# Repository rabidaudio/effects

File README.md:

# Custom effects pedals

Homemade guitar/bass effects pedals.

- [Splitter](/splitter)
- [Bass Chorus (WIP)](/chorus)

## License

Schematics, board layouts, documentation, etc. is licensed under [Creative Commons Attribution-NonCommercial-ShareAlike 4.0 International License](http://creativecommons.org/licenses/by-nc-sa/4.0/).

If you're interested in commercial use, please ask first.

Any source code is licensed under [MIT](SOFTWARE_LICENSE).

## Notes

```
jacks: neutrik from shared effects lib
capacitors: Capacitor_THT:C_Rect_L7.0mm_W2.5mm_P5.00mm
resistors (flush): Resistor_THT:R_Axial_DIN0207_L6.3mm_D2.5mm_P10.16mm_Horizontal
alpha 9mm pots: Potentiometer_THT:Potentiometer_Alpha_RD901F-40-00D_Single_Vertical

CASE:
outer dims: 120x65 mm
wall depth: 2 mm
usable inner space: 102x60 mm
screw area: 8.6x8.6 mm

center point: 160.02 x 101.6 mm

pots minimum 12mm from top
stomp switch ~34mm from bottom
```

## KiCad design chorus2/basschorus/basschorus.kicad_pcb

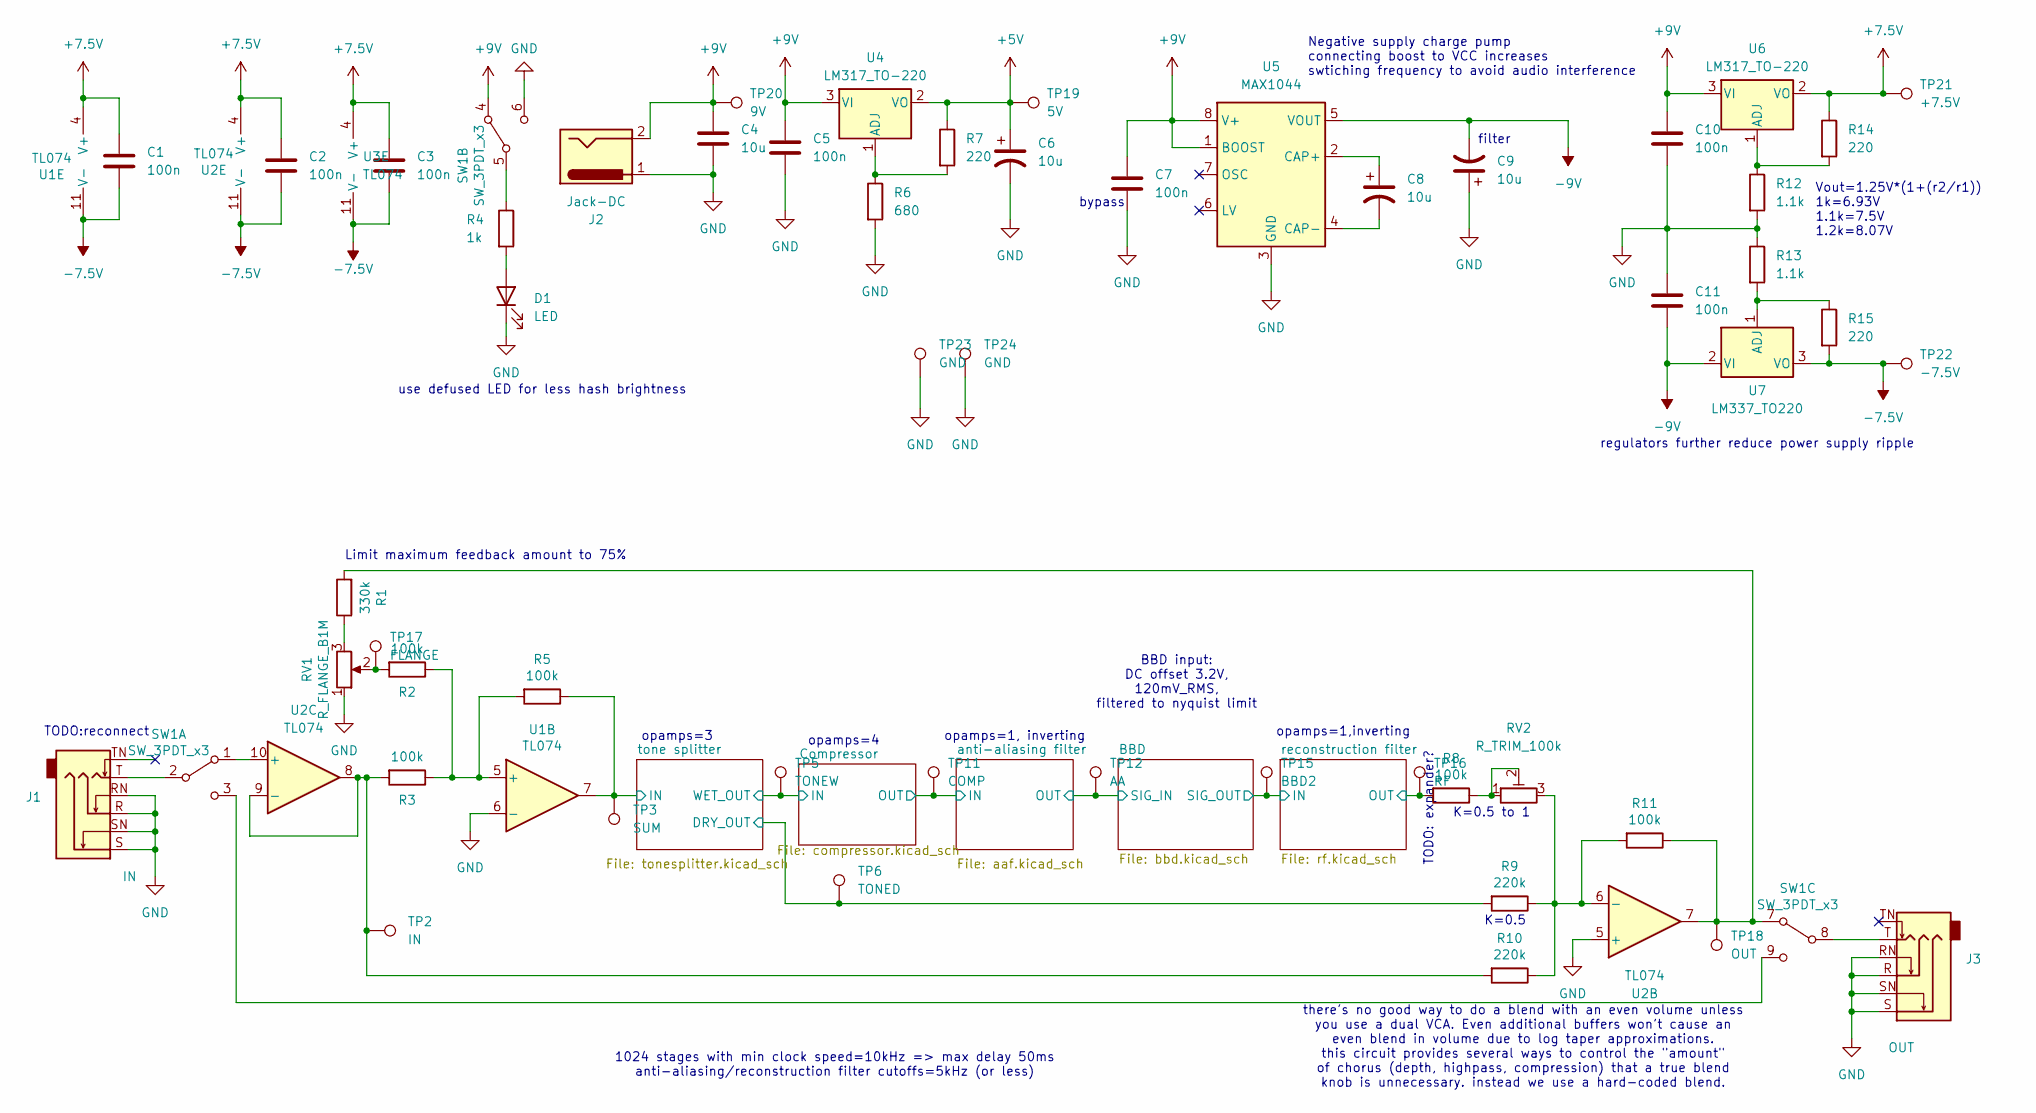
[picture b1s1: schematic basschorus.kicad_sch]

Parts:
C1, C2, C3, C5, C7, C10, C11: 100n; C_Rect_L7.0mm_W2.5mm_P5.00mm
C4, C6, C8, C9: 10u; CP_Radial_D8.0mm_P5.00mm
D1: LED; LED_Rectangular_W5.0mm_H2.0mm
J1: IN; JackHeaders
J2: Jack-DC; PinSocket_1x02_P2.54mm_Vertical
J3: OUT; JackHeaders
R1: 330k; R_Axial_DIN0204_L3.6mm_D1.6mm_P2.54mm_Vertical
R2, R3, R5, R8, R11: 100k; R_Axial_DIN0204_L3.6mm_D1.6mm_P2.54mm_Vertical
R4: 1k; R_Axial_DIN0204_L3.6mm_D1.6mm_P2.54mm_Vertical
R6: 680; R_Axial_DIN0204_L3.6mm_D1.6mm_P2.54mm_Vertical
R7, R14, R15: 220; R_Axial_DIN0204_L3.6mm_D1.6mm_P2.54mm_Vertical
R9, R10: 220k; R_Axial_DIN0204_L3.6mm_D1.6mm_P2.54mm_Vertical
R12, R13: 1.1k; R_Axial_DIN0204_L3.6mm_D1.6mm_P2.54mm_Vertical
RV1: R_FLANGE_B1M; Potentiometer_Alpha_RD901F-40-00D_Single_Vertical_CircularH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
RV2: R_TRIM_100k; Potentiometer_Vishay_T73YP_Vertical
SW1: SW_3PDT_x3; PinHeader_1x09_P2.54mm_Vertical
TP2: IN; TestPoint_THTPad_2.5x2.5mm_Drill1.2mm
TP3: SUM; TestPoint_THTPad_2.5x2.5mm_Drill1.2mm
TP5: TONEW; TestPoint_THTPad_2.5x2.5mm_Drill1.2mm
TP6: TONED; TestPoint_THTPad_2.5x2.5mm_Drill1.2mm
TP11: COMP; TestPoint_THTPad_2.5x2.5mm_Drill1.2mm
TP12: AA; TestPoint_THTPad_2.5x2.5mm_Drill1.2mm
TP15: BBD2; TestPoint_THTPad_2.5x2.5mm_Drill1.2mm
TP16: RF; TestPoint_THTPad_2.5x2.5mm_Drill1.2mm
TP17: FLANGE; TestPoint_THTPad_2.5x2.5mm_Drill1.2mm
TP18: OUT; TestPoint_THTPad_2.5x2.5mm_Drill1.2mm
TP19: 5V; TestPoint_THTPad_2.5x2.5mm_Drill1.2mm
TP20: 9V; TestPoint_THTPad_2.5x2.5mm_Drill1.2mm
TP21: +7.5V; TestPoint_THTPad_2.5x2.5mm_Drill1.2mm
TP22: -7.5V; TestPoint_THTPad_2.5x2.5mm_Drill1.2mm
TP23, TP24: GND; TestPoint_THTPad_2.5x2.5mm_Drill1.2mm
U1, U2, U3: TL074; SO-14_3.9x8.65mm_P1.27mm
U4, U6: LM317_TO-220; TO-220-3_Vertical
U5: MAX1044; DIP-8_W7.62mm
U7: LM337_TO220; TO-220-3_Vertical

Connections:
+5V: C6.1, R7.1, TP19.1, U4.2 (VO); also elsewhere on the board
+7.5V: C1.1, C2.1, C3.1, R14.1, TP21.1, U1.4 (V+), U2.4 (V+), U3.4 (V+), U6.2 (VO)
+9V: C4.1, C5.1, C7.1, C10.1, J2.2, SW1.4 (A), TP20.1, U4.3 (VI), U5.1 (BOOST), U5.8 (V+), U6.3 (VI)
-7.5V: C1.2, C2.2, C3.2, R15.2, TP22.1, U1.11 (V-), U2.11 (V-), U3.11 (V-), U7.3 (VO)
-9V: C9.2, C11.2, U5.5 (VOUT), U7.2 (VI)
/BBD/SIG_IN: TP12.1; also elsewhere on the board
/BBD/SIG_OUT: TP15.1; also elsewhere on the board
/Compressor/IN: TP5.1; also elsewhere on the board
/Compressor/OUT: TP11.1; also elsewhere on the board
/reconstruction filter/OUT: R8.2, TP16.1; also elsewhere on the board
/tone splitter/DRY_OUT: R9.2, TP6.1; also elsewhere on the board
/tone splitter/IN: R5.1, TP3.1, U1.7; also elsewhere on the board
GND: C4.2, C5.2, C6.2, C7.2, C9.1, C10.2, C11.1, D1.1 (K), J1.R, J1.RN, J1.S, J1.SN, J2.1, J3.R, J3.RN, J3.S, J3.SN, R6.2, R12.2, R13.1, RV1.1, SW1.6 (C), TP23.1, TP24.1, U1.6 (-), U2.5 (+), U5.3 (GND); also elsewhere on the board
unnamed: D1.2 (A), R4.2
unnamed: R1.1, RV1.3
unnamed: R2.2, RV1.2, TP17.1
unnamed: R8.1, RV2.1, RV2.2
unnamed: SW1.1 (A), U2.10 (+)
unnamed: J1.T, SW1.2 (B)
unnamed: SW1.3 (C), SW1.9 (C)
unnamed: R4.1, SW1.5 (B)
unnamed: R1.2, R11.1, SW1.7 (A), TP18.1, U2.7
unnamed: J3.T, SW1.8 (B)
unnamed: R2.1, R3.1, R5.2, U1.5 (+)
unnamed: R9.1, R10.1, R11.2, RV2.3, U2.6 (-)
unnamed: R3.2, R10.2, TP2.1, U2.8, U2.9 (-)
unnamed: R6.1, R7.2, U4.1 (ADJ)
unnamed: C8.1, U5.2 (CAP+)
unnamed: C8.2, U5.4 (CAP-)
unnamed: R12.1, R14.2, U6.1 (ADJ)
unnamed: R13.2, R15.1, U7.1 (ADJ)

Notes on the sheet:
TODO: expander?
Vout=1.25V*(1+(r2/r1)) 1k=6.93V 1.1k=7.5V 1.2k=8.07V
opamps=1,inverting
TODO:reconnect
opamps=1, inverting
Negative supply charge pump connecting boost to VCC increases swtiching frequency to avoid audio interference
K=0.5
regulators further reduce power supply ripple
opamps=4
bypass
filter
use defused LED for less hash brightness
K=0.5 to 1
there's no good way to do a blend with an even volume unless you use a dual VCA. Even additional buffers won't cause an even blend in volume due to log taper approximations. this circuit provides several ways to control the "amount" of chorus (depth, highpass, compression) that a true blend knob is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
opamps=3
BBD input: DC offset 3.2V, 120mV_RMS, filtered to nyquist limit
Limit maximum feedback amount to 75%
1024 stages with min clock speed=10kHz => max delay 50ms anti-aliasing/reconstruction filter cutoffs=5kHz (or less)

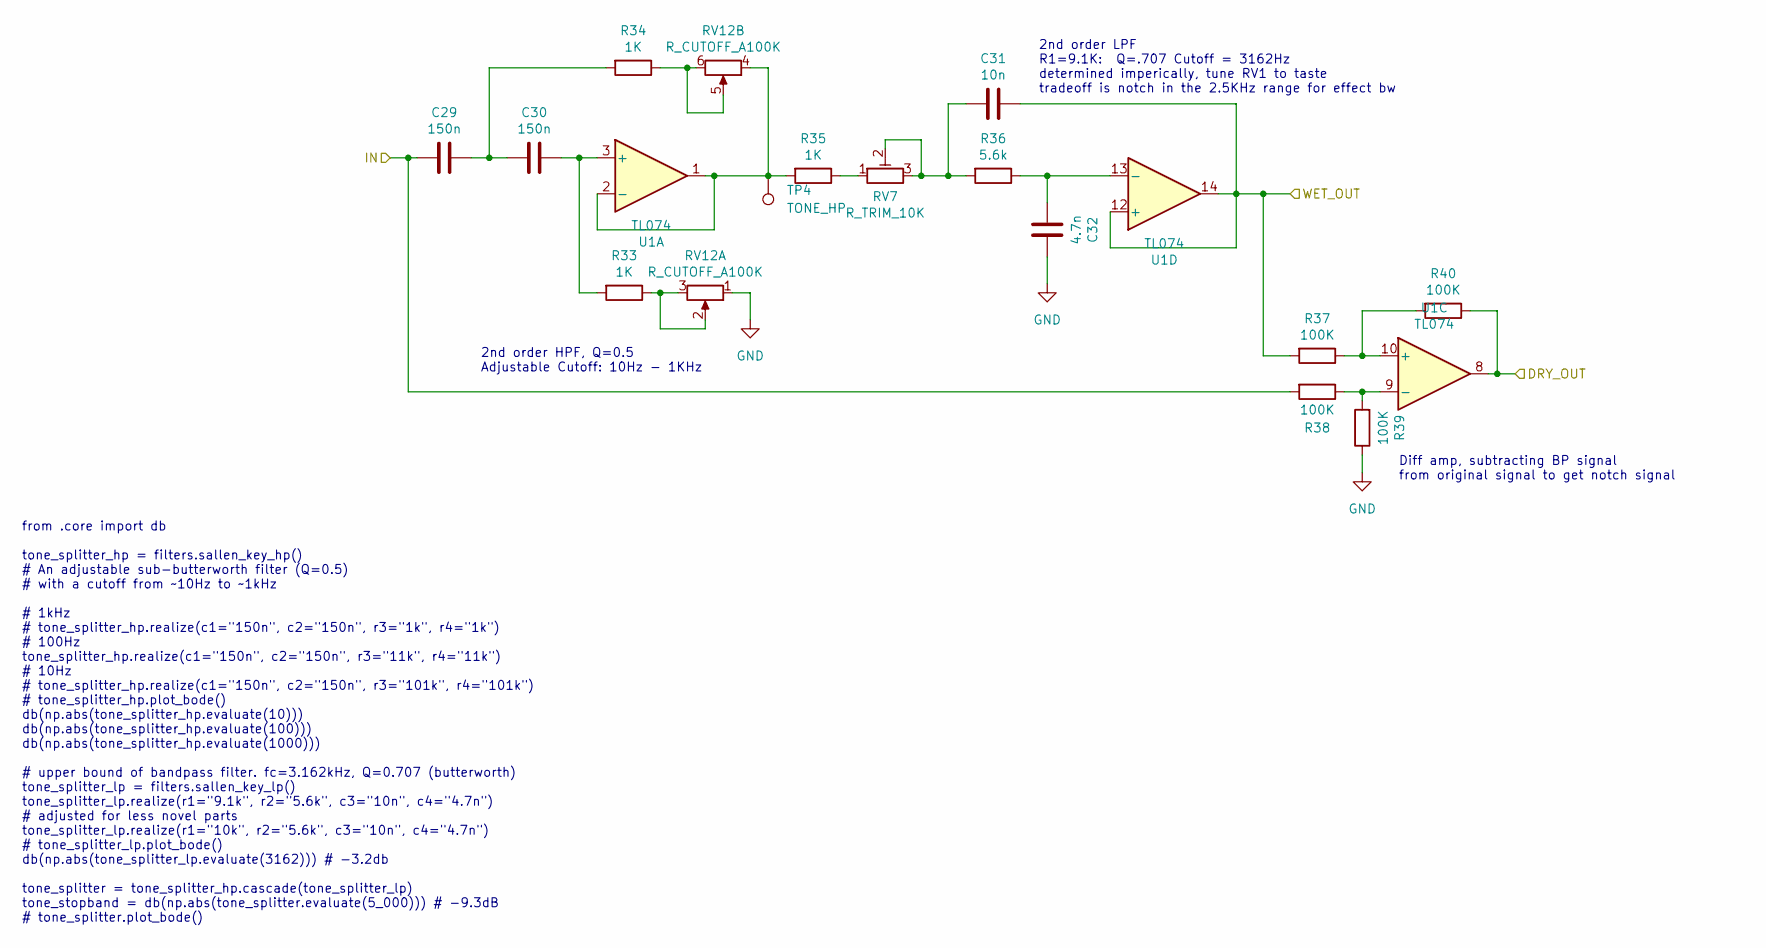
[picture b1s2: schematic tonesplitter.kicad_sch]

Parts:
C29, C30: 150n; C_Rect_L7.0mm_W2.5mm_P5.00mm
C31: 10n; C_Rect_L7.0mm_W2.5mm_P5.00mm
C32: 4.7n; C_Rect_L7.0mm_W2.5mm_P5.00mm
R33, R34, R35: 1K; R_Axial_DIN0204_L3.6mm_D1.6mm_P2.54mm_Vertical
R36: 5.6k; R_Axial_DIN0204_L3.6mm_D1.6mm_P2.54mm_Vertical
R37, R38, R39, R40: 100K; R_Axial_DIN0204_L3.6mm_D1.6mm_P2.54mm_Vertical
RV7: R_TRIM_10K; Potentiometer_Vishay_T73YP_Vertical
RV12: R_CUTOFF_A100K; Potentiometer_Alpha_RD902F-40-00D_Dual_Vertical_CircularHol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
TP4: TONE_HP; TestPoint_THTPad_2.5x2.5mm_Drill1.2mm
U1: TL074; SO-14_3.9x8.65mm_P1.27mm

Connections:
/Compressor/IN: C31.1, R37.2, U1.12 (+), U1.14; also elsewhere on the board
/tone splitter/DRY_OUT: R40.1, U1.8; also elsewhere on the board
/tone splitter/IN: C29.2, R38.2; also elsewhere on the board
GND: C32.1, R39.1, RV12.1; also elsewhere on the board
unnamed: C29.1, C30.2, R34.2
unnamed: C31.2, R36.2, RV7.2, RV7.3
unnamed: R33.1, RV12.2, RV12.3
unnamed: R34.1, RV12.5, RV12.6
unnamed: R35.1, RV7.1
unnamed: C30.1, R33.2, U1.3 (+)
unnamed: R35.2, RV12.4, TP4.1, U1.1, U1.2 (-)
unnamed: R37.1, R40.2, U1.10 (+)
unnamed: R38.1, R39.2, U1.9 (-)
unnamed: C32.2, R36.1, U1.13 (-)

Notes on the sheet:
Diff amp, subtracting BP signal from original signal to get notch signal
2nd order LPF R1=9.1K: Q=.707 Cutoff = 3162Hz determined imperically, tune RV1 to taste tradeoff is notch in the 2.5KHz range for effect bw
2nd order HPF, Q=0.5 Adjustable Cutoff: 10Hz - 1KHz
from .core import db tone_splitter_hp = filters.sallen_key_hp() # An adjustable sub-butterworth filter (Q=0.5) # with a cutoff from ~10Hz to ~1kHz # 1kHz # tone_splitter_hp.realize(c1="150n", c2="150n", r3="1k", r4="1k") # 100Hz tone_splitter_hp.realize(c1="150n", c2="150n", r3="11k", r4="11k") # 1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

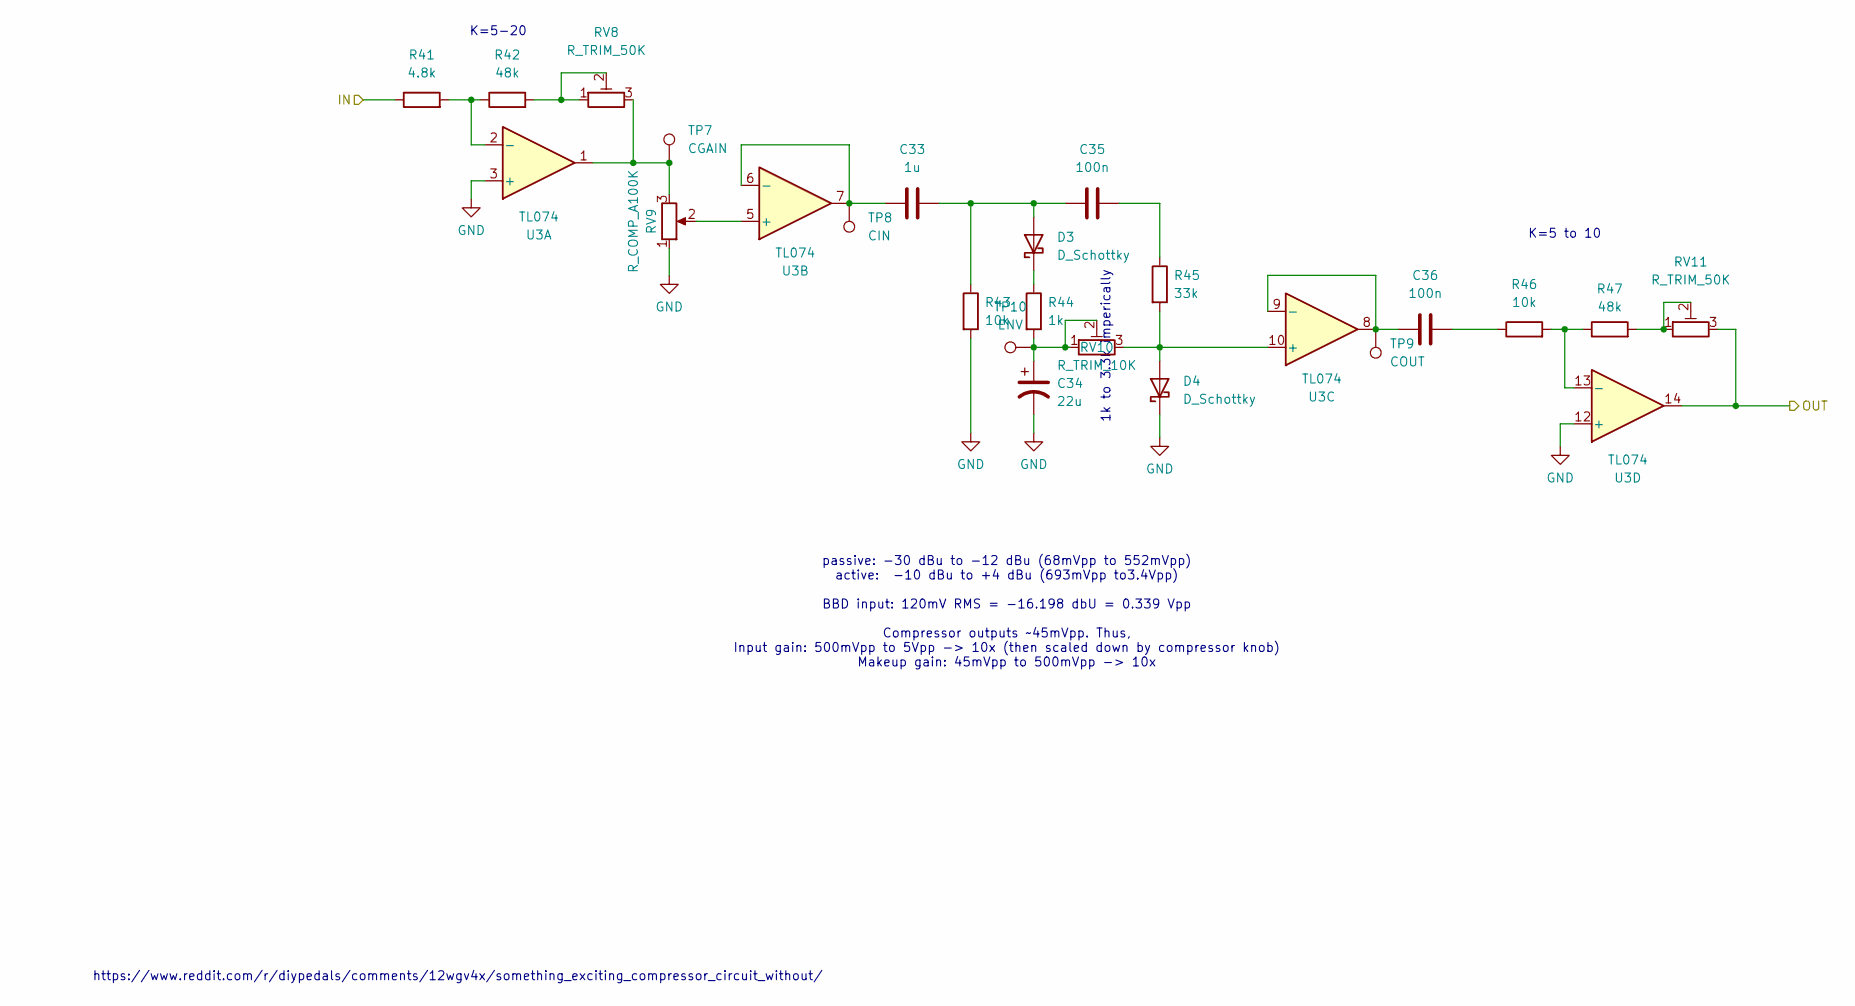
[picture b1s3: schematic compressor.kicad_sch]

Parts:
C33: 1u; C_Rect_L7.0mm_W2.5mm_P5.00mm
C34: 22u; CP_Radial_D8.0mm_P5.00mm
C35, C36: 100n; C_Rect_L7.0mm_W2.5mm_P5.00mm
D3, D4: D_Schottky; D_DO-34_SOD68_P7.62mm_Horizontal
R41: 4.8k; R_Axial_DIN0204_L3.6mm_D1.6mm_P2.54mm_Vertical
R42, R47: 48k; R_Axial_DIN0204_L3.6mm_D1.6mm_P2.54mm_Vertical
R43, R46: 10k; R_Axial_DIN0204_L3.6mm_D1.6mm_P2.54mm_Vertical
R44: 1k; R_Axial_DIN0204_L3.6mm_D1.6mm_P2.54mm_Vertical
R45: 33k; R_Axial_DIN0204_L3.6mm_D1.6mm_P2.54mm_Vertical
RV8, RV11: R_TRIM_50K; Potentiometer_Vishay_T73YP_Vertical
RV9: R_COMP_A100K; Potentiometer_Alpha_RD901F-40-00D_Single_Vertical_CircularH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
RV10: R_TRIM_10K; Potentiometer_Vishay_T73YP_Vertical
TP7: CGAIN; TestPoint_THTPad_2.5x2.5mm_Drill1.2mm
TP8: CIN; TestPoint_THTPad_2.5x2.5mm_Drill1.2mm
TP9: COUT; TestPoint_THTPad_2.5x2.5mm_Drill1.2mm
TP10: ENV; TestPoint_THTPad_2.5x2.5mm_Drill1.2mm
U3: TL074; SO-14_3.9x8.65mm_P1.27mm

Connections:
/Compressor/IN: R41.1; also elsewhere on the board
/Compressor/OUT: RV11.3, U3.14; also elsewhere on the board
GND: C34.2, D4.1 (K), R43.2, RV9.1, U3.3 (+), U3.12 (+); also elsewhere on the board
unnamed: C34.1, R44.2, RV10.1, RV10.2, TP10.1
unnamed: C35.2, R45.1
unnamed: C36.2, R46.1
unnamed: C33.2, C35.1, D3.2 (A), R43.1
unnamed: D3.1 (K), R44.1
unnamed: D4.2 (A), R45.2, RV10.3, U3.10 (+)
unnamed: R42.2, RV8.1, RV8.2
unnamed: R47.2, RV11.1, RV11.2
unnamed: RV8.3, RV9.3, TP7.1, U3.1
unnamed: R41.2, R42.1, U3.2 (-)
unnamed: RV9.2, U3.5 (+)
unnamed: C33.1, TP8.1, U3.6 (-), U3.7
unnamed: C36.1, TP9.1, U3.8, U3.9 (-)
unnamed: R46.2, R47.1, U3.13 (-)

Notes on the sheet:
1k to 3.3k imperically
https://www.reddit.com/r/diypedals/comments/12wgv4x/something_exciting_compressor_circuit_without/
passive: -30 dBu to -12 dBu (68mVpp to 552mVpp) active: -10 dBu to +4 dBu (693mVpp to3.4Vpp) BBD input: 120mV RMS = -16.198 dbU = 0.339 Vpp Compressor outputs ~45mVpp. Thus, Input gain: 500mVpp to 5Vpp -> 10x (then scaled down by compressor knob) Makeup gain: 45mVpp to 500mVpp -> 10x
K=5-20
K=5 to 10

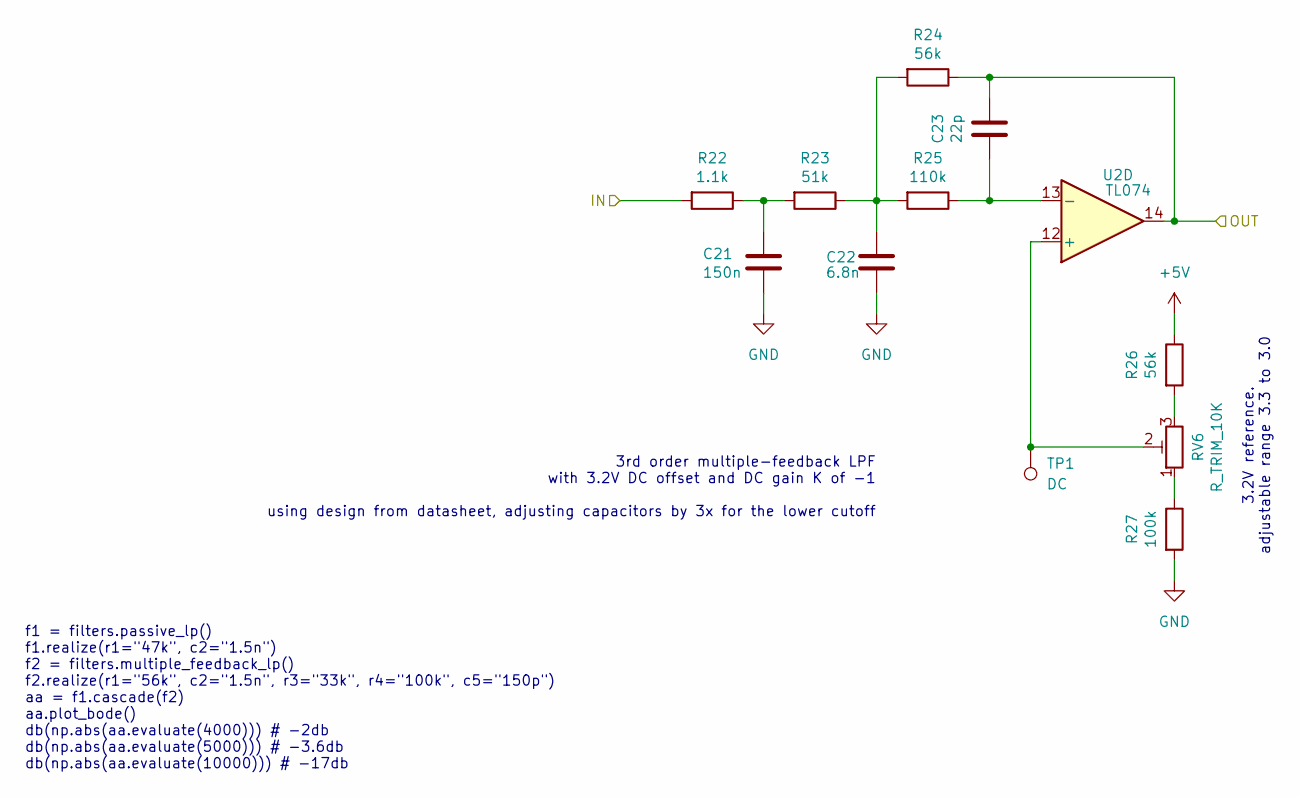
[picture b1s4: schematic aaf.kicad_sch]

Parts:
C21: 150n; C_Rect_L7.0mm_W2.5mm_P5.00mm
C22: 6.8n; C_Rect_L7.0mm_W2.5mm_P5.00mm
C23: 22p; C_Rect_L7.0mm_W2.5mm_P5.00mm
R22: 1.1k; R_Axial_DIN0204_L3.6mm_D1.6mm_P2.54mm_Vertical
R23: 51k; R_Axial_DIN0204_L3.6mm_D1.6mm_P2.54mm_Vertical
R24, R26: 56k; R_Axial_DIN0204_L3.6mm_D1.6mm_P2.54mm_Vertical
R25: 110k; R_Axial_DIN0204_L3.6mm_D1.6mm_P2.54mm_Vertical
R27: 100k; R_Axial_DIN0204_L3.6mm_D1.6mm_P2.54mm_Vertical
RV6: R_TRIM_10K; Potentiometer_Vishay_T73YP_Vertical
TP1: DC; TestPoint_THTPad_2.5x2.5mm_Drill1.2mm
U2: TL074; SO-14_3.9x8.65mm_P1.27mm

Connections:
+5V: R26.1; also elsewhere on the board
/BBD/SIG_IN: C23.1, R24.1, U2.14; also elsewhere on the board
/Compressor/OUT: R22.2; also elsewhere on the board
GND: C21.1, C22.1, R27.2; also elsewhere on the board
unnamed: C21.2, R22.1, R23.2
unnamed: C22.2, R23.1, R24.2, R25.2
unnamed: R26.2, RV6.3
unnamed: R27.1, RV6.1
unnamed: RV6.2, TP1.1, U2.12 (+)
unnamed: C23.2, R25.1, U2.13 (-)

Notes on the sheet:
f1 = filters.passive_lp() f1.realize(r1="47k", c2="1.5n") f2 = filters.multiple_feedback_lp() f2.realize(r1="56k", c2="1.5n", r3="33k", r4="100k", c5="150p") aa = f1.cascade(f2) aa.plot_bode() db(np.abs(aa.evaluate(4000))) # -2db db(np.abs(aa.evaluate(5000))) # -3.6db db(np.abs(aa.evaluate(10000)))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
3rd order multiple-feedback LPF with 3.2V DC offset and DC gain K of -1 using design from datasheet, adjusting capacitors by 3x for the lower cutoff
3.2V reference. adjustable range 3.3 to 3.0

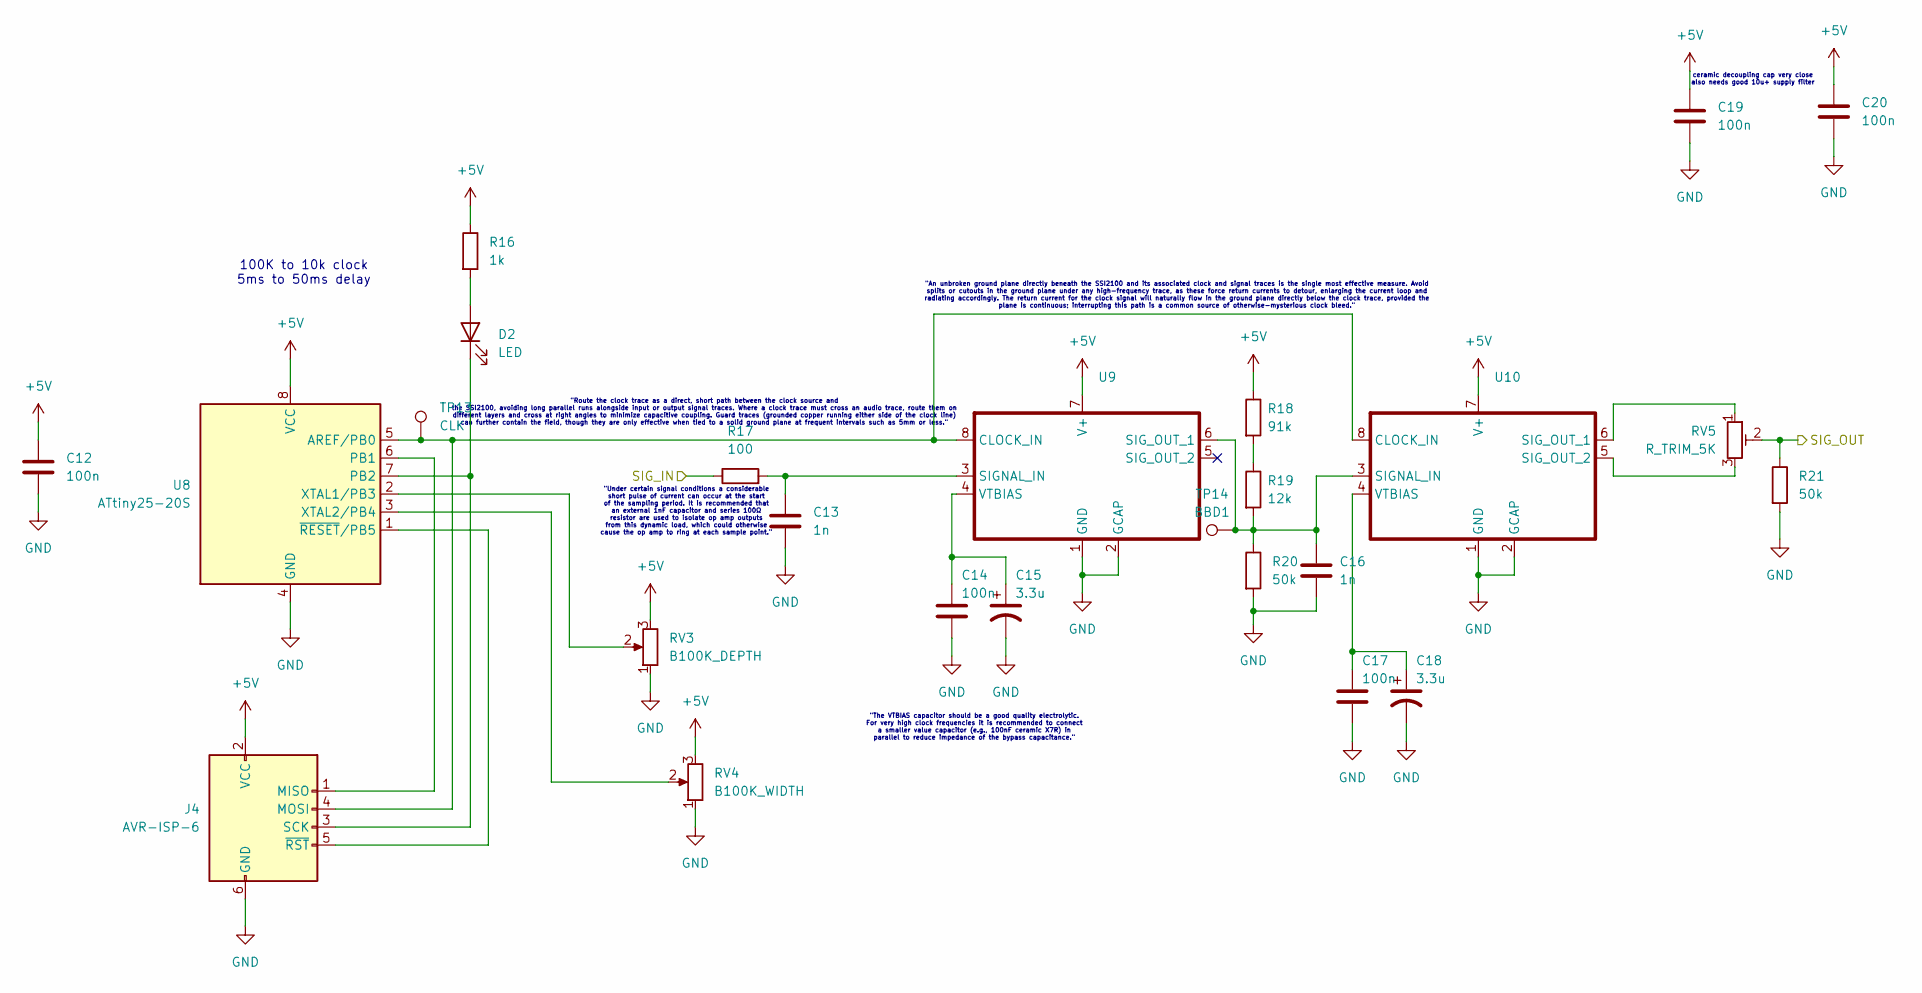
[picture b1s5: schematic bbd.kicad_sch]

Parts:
C12, C14, C17, C19, C20: 100n; C_Rect_L7.0mm_W2.5mm_P5.00mm
C13, C16: 1n; C_Rect_L7.0mm_W2.5mm_P5.00mm
C15, C18: 3.3u; CP_Radial_D8.0mm_P5.00mm
D2: LED; LED_Rectangular_W5.0mm_H2.0mm
J4: AVR-ISP-6; PinHeader_2x03_P2.54mm_Vertical
R16: 1k; R_Axial_DIN0204_L3.6mm_D1.6mm_P2.54mm_Vertical
R17: 100; R_Axial_DIN0204_L3.6mm_D1.6mm_P2.54mm_Vertical
R18: 91k; R_Axial_DIN0204_L3.6mm_D1.6mm_P2.54mm_Vertical
R19: 12k; R_Axial_DIN0204_L3.6mm_D1.6mm_P2.54mm_Vertical
R20, R21: 50k; R_Axial_DIN0204_L3.6mm_D1.6mm_P2.54mm_Vertical
RV3: B100K_DEPTH; Potentiometer_Alpha_RD901F-40-00D_Single_Vertical_CircularH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
RV4: B100K_WIDTH; Potentiometer_Alpha_RD901F-40-00D_Single_Vertical_CircularH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
RV5: R_TRIM_5K; Potentiometer_Vishay_T73YP_Vertical
TP13: CLK; TestPoint_THTPad_2.5x2.5mm_Drill1.2mm
TP14: BBD1; TestPoint_THTPad_2.5x2.5mm_Drill1.2mm
U8: ATtiny25-20S; DIP-8_W7.62mm
U9, U10: SOP-8_3.76x4.96mm_P1.27mm

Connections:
+5V: C12.1, C19.1, C20.1, J4.2 (VCC), R16.1, R18.1, RV3.3, RV4.3, U8.8 (VCC), U9.7 (V+), U10.7 (V+); also elsewhere on the board
/BBD/SIG_IN: R17.1; also elsewhere on the board
/BBD/SIG_OUT: R21.1, RV5.2; also elsewhere on the board
GND: C12.2, C13.2, C14.2, C15.2, C16.2, C17.2, C18.2, C19.2, C20.2, J4.6 (GND), R20.2, R21.2, RV3.1, RV4.1, U8.4 (GND), U9.1 (GND), U9.2 (GCAP), U10.1 (GND), U10.2 (GCAP); also elsewhere on the board
unnamed: D2.2 (A), R16.2
unnamed: D2.1 (K), J4.3 (SCK), U8.7 (PB2)
unnamed: J4.1 (MISO), U8.6 (PB1)
unnamed: J4.4 (MOSI), TP13.1, U8.5 (AREF/PB0), U9.8 (CLOCK_IN), U10.8 (CLOCK_IN)
unnamed: J4.5 (~RST), U8.1 (~RESET/PB5)
unnamed: R18.2, R19.1
unnamed: RV3.2, U8.2 (XTAL1/PB3)
unnamed: RV4.2, U8.3 (XTAL2/PB4)
unnamed: C13.1, R17.2, U9.3 (SIGNAL_IN)
unnamed: C14.1, C15.1, U9.4 (VTBIAS)
unnamed: C16.1, R19.2, R20.1, TP14.1, U9.6 (SIG_OUT_1), U10.3 (SIGNAL_IN)
unnamed: RV5.1, U10.6 (SIG_OUT_1)
unnamed: RV5.3, U10.5 (SIG_OUT_2)
unnamed: C17.1, C18.1, U10.4 (VTBIAS)

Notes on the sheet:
"The VTBIAS capacitor should be a good quality electrolytic. For very high clock frequencies it is recommended to connect a smaller value capacitor (e.g., 100nF ceramic X7R) in parallel to reduce impedance of the bypass capacitance."
"An unbroken ground plane directly beneath the SSI2100 and its associated clock and signal traces is the single most effective measure. Avoid splits or cutouts in the ground plane under any high-frequency trace, as these force return currents to detour, enlarging the current loop and radiating acco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
"Route the clock trace as a direct, short path between the clock source and the SSI2100, avoiding long parallel runs alongside input or output signal traces. Where a clock trace must cross an audio trace, route them on different layers and cross at right angles to minimize capacitive coupling. Guar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
"Under certain signal conditions a considerable short pulse of current can occur at the start of the sampling period. It is recommended that an external 1nF capacitor and series 100Ω resistor are used to isolate op amp outputs from this dynamic load, which could otherwise cause the op amp to ring a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
ceramic decoupling cap very close also needs good 10u+ supply filter
100K to 10k clock 5ms to 50ms delay

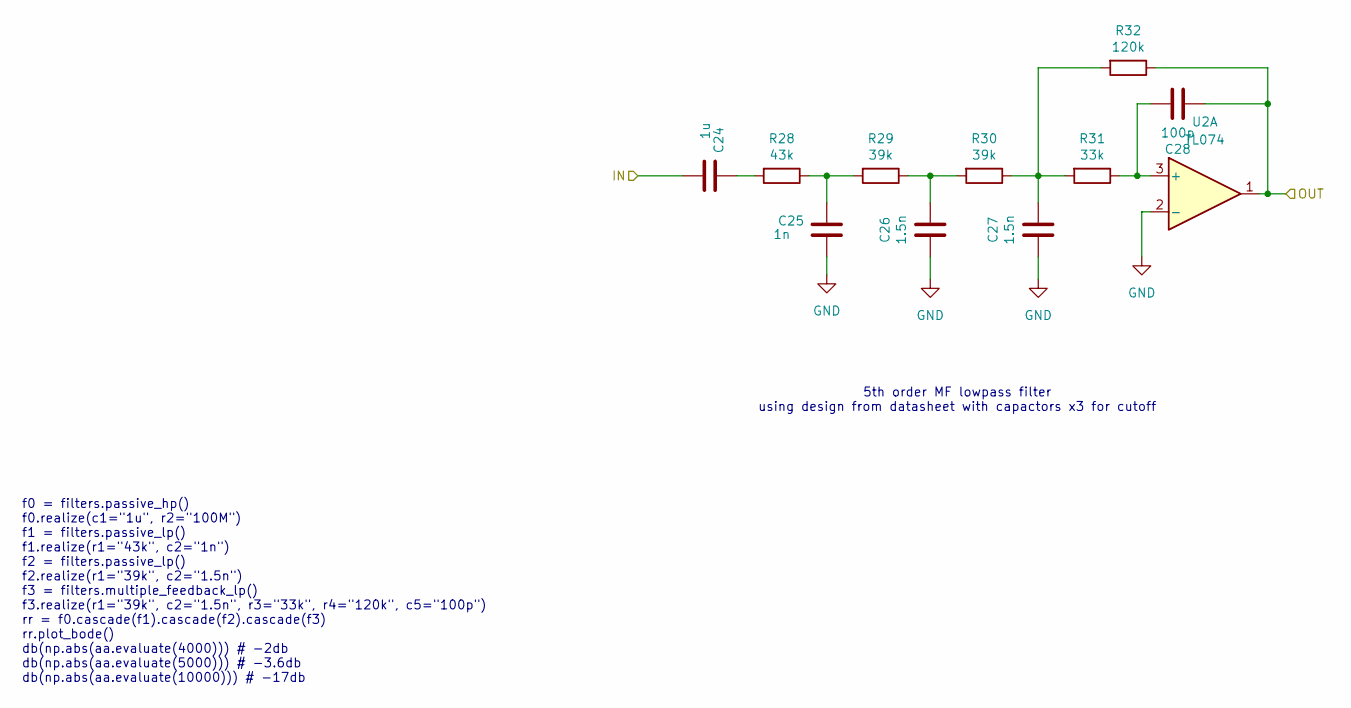
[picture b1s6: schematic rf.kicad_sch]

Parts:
C24: 1u; C_Rect_L7.0mm_W2.5mm_P5.00mm
C25: 1n; C_Rect_L7.0mm_W2.5mm_P5.00mm
C26, C27: 1.5n; C_Rect_L7.0mm_W2.5mm_P5.00mm
C28: 100p; C_Rect_L7.0mm_W2.5mm_P5.00mm
R28: 43k; R_Axial_DIN0204_L3.6mm_D1.6mm_P2.54mm_Vertical
R29, R30: 39k; R_Axial_DIN0204_L3.6mm_D1.6mm_P2.54mm_Vertical
R31: 33k; R_Axial_DIN0204_L3.6mm_D1.6mm_P2.54mm_Vertical
R32: 120k; R_Axial_DIN0204_L3.6mm_D1.6mm_P2.54mm_Vertical
U2: TL074; SO-14_3.9x8.65mm_P1.27mm

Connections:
/BBD/SIG_OUT: C24.1; also elsewhere on the board
/reconstruction filter/OUT: C28.2, R32.1, U2.1; also elsewhere on the board
GND: C25.1, C26.2, C27.2, U2.2 (-); also elsewhere on the board
unnamed: C24.2, R28.2
unnamed: C25.2, R28.1, R29.2
unnamed: C26.1, R29.1, R30.2
unnamed: C27.1, R30.1, R31.2, R32.2
unnamed: C28.1, R31.1, U2.3 (+)

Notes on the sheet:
5th order MF lowpass filter using design from datasheet with capactors x3 for cutoff
f0 = filters.passive_hp() f0.realize(c1="1u", r2="100M") f1 = filters.passive_lp() f1.realize(r1="43k", c2="1n") f2 = filters.passive_lp() f2.realize(r1="39k", c2="1.5n") f3 = filters.multiple_feedback_lp() f3.realize(r1="39k", c2="1.5n", r3="33k", r4="120k", c5="100p") rr = f0.cascade(f1).cascade(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

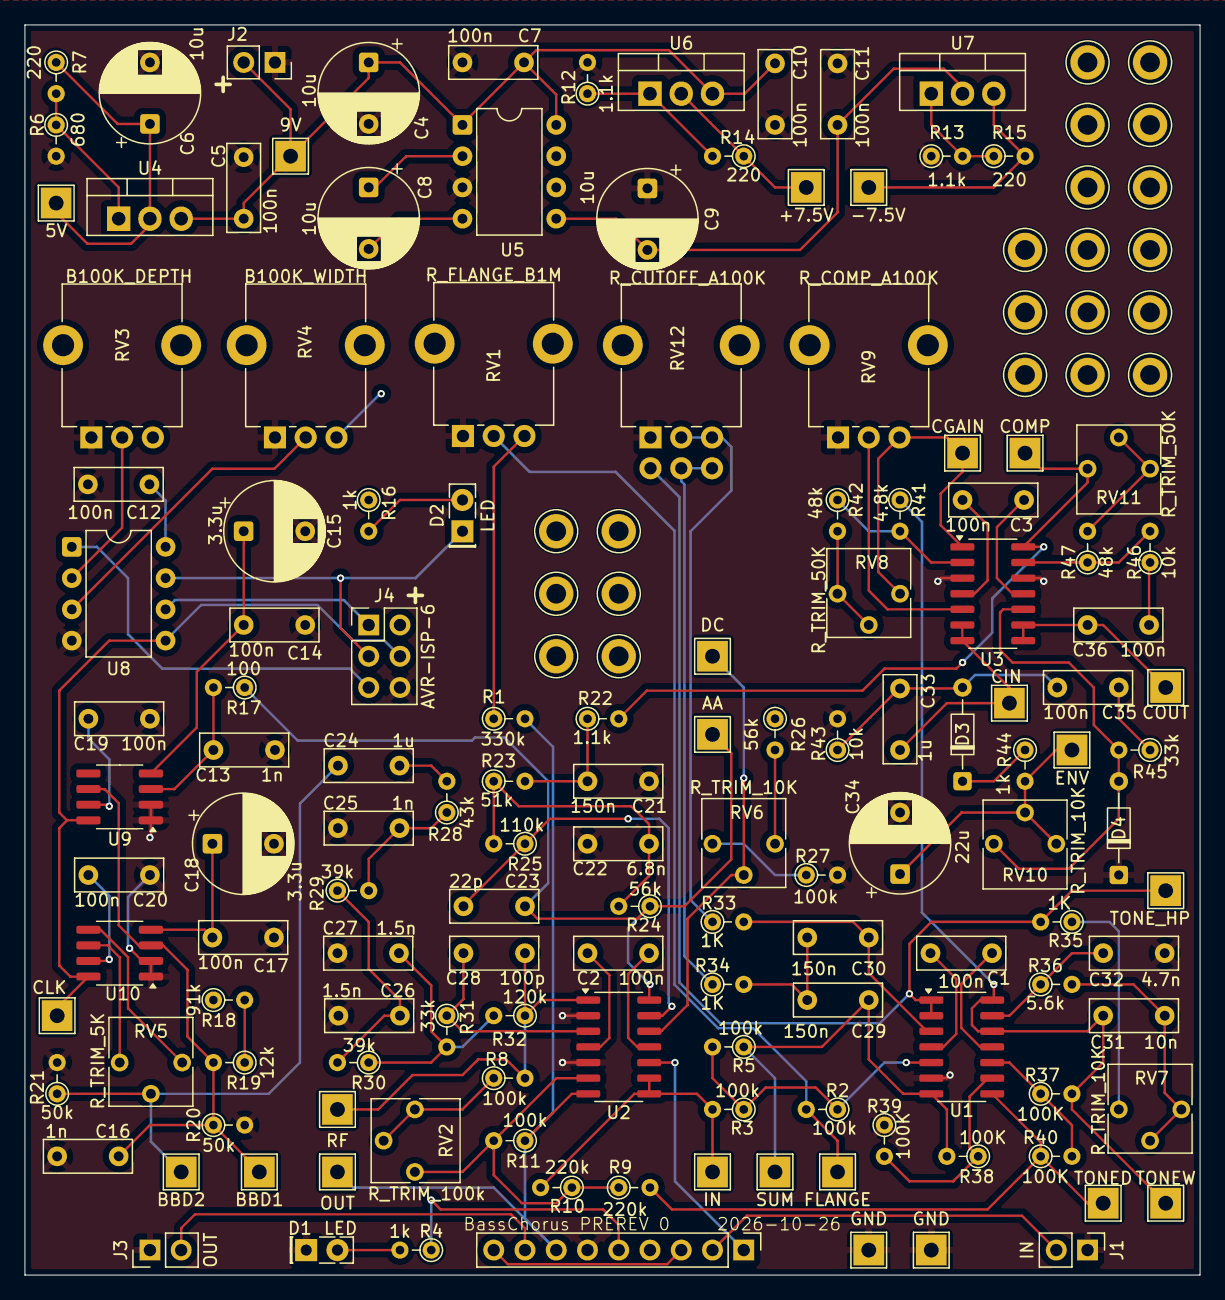
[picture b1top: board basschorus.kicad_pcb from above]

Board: 4 copper layers, 95.5 x 101.6 mm, 138 parts (0 on the bottom side), 80 nets.
